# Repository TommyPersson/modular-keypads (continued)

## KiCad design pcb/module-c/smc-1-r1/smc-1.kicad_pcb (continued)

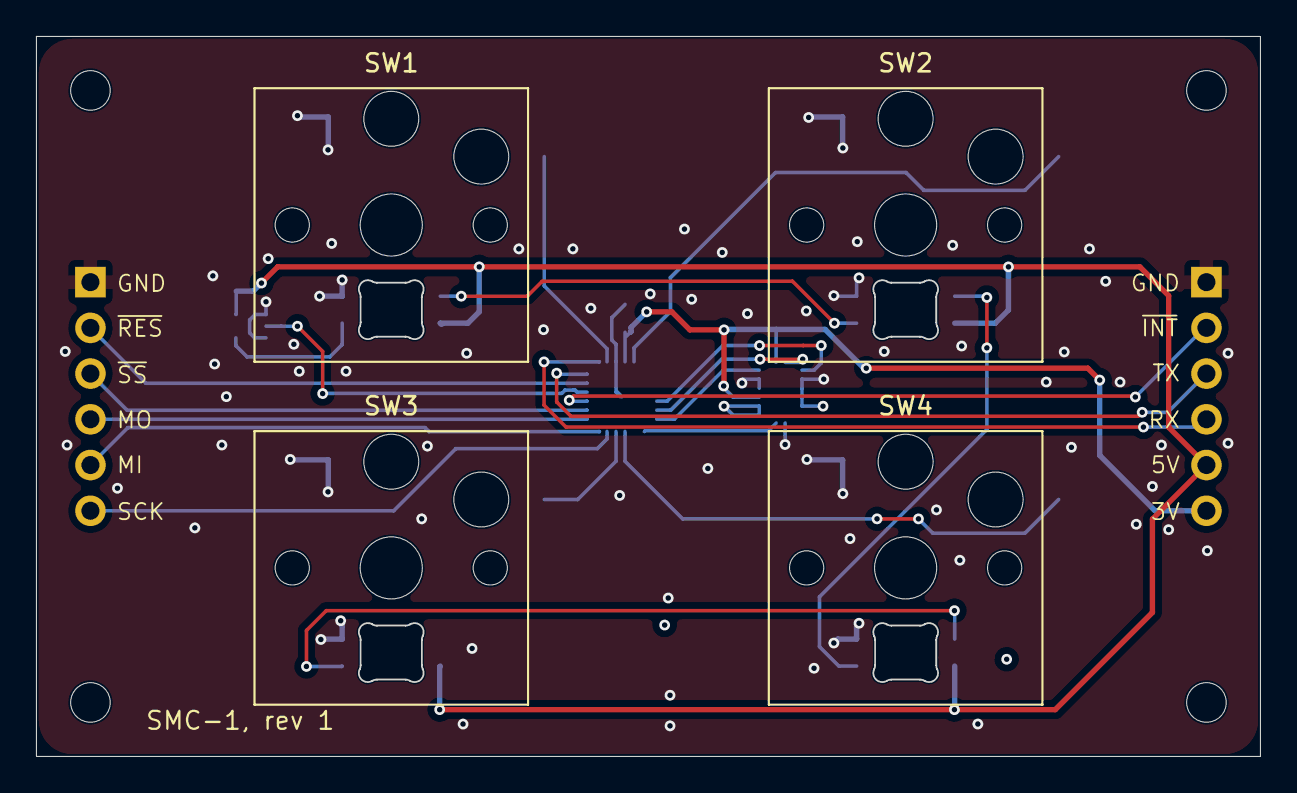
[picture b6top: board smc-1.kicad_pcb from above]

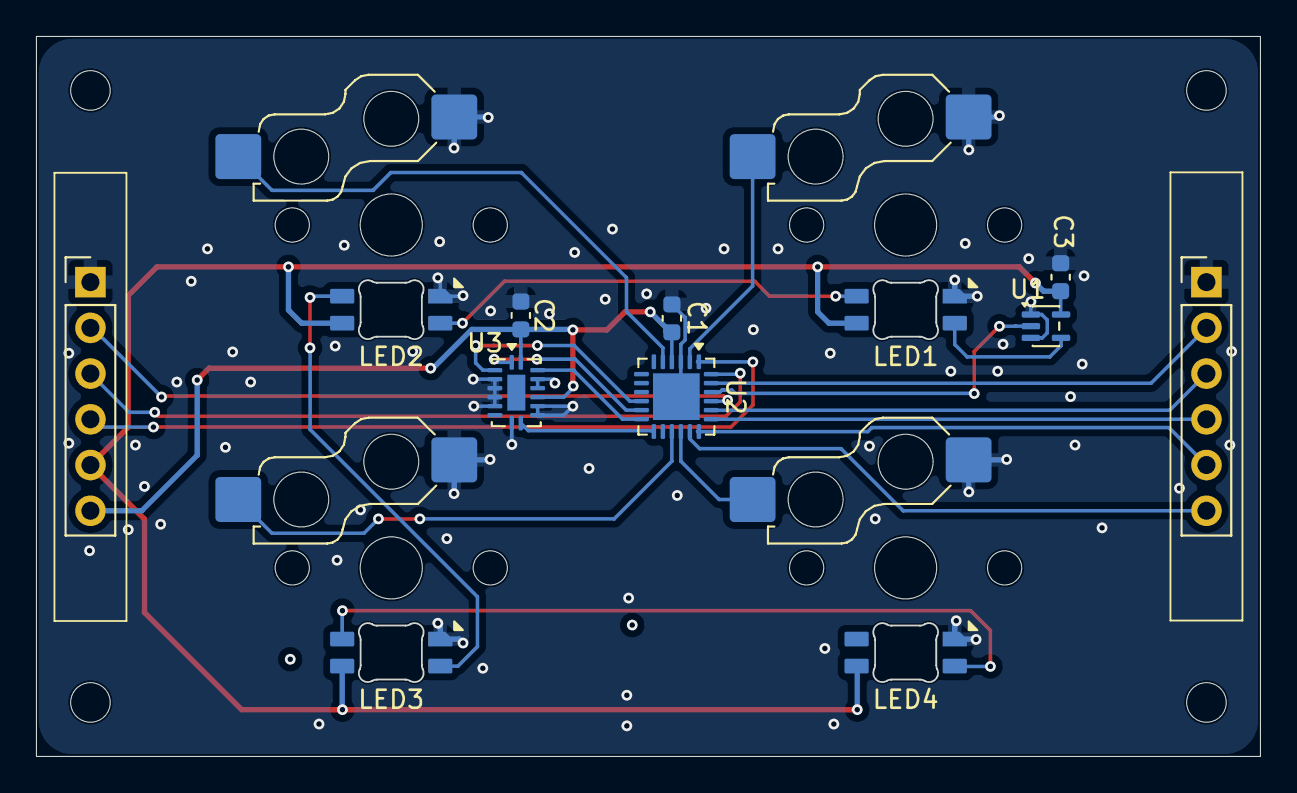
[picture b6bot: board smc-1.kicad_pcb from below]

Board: 4 copper layers, 68.0 x 40.0 mm, 20 parts (12 on the bottom side), 24 nets.

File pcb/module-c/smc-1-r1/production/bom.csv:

Designator,Footprint,Quantity,Value,LCSC Part #
"C1, C2",0603,2,0.1,
C3,0603,1,0.1 uF,
"J1, J3",PinHeader_1x06_P2.54mm_Vertical,2,Conn_01x06,
"LED1, LED2, LED3, LED4, LED5, LED6",LED_choc_6028R-ROT,6,SK6812MINI-E,
"SW1, SW2, SW3, SW4, SW5, SW6",SW_Hotswap_Kailh_Choc_V1_1.00u,6,SW_Push,
U1,SOT-353_SC-70-5,1,74AHCT1G125,
U2,QFN-24-1EP_4x4mm_P0.5mm_EP2.6x2.6mm,1,ATtiny1616-M,
U3,DHVQFN-16-1EP_2.5x3.5mm_P0.5mm_EP1x2mm,1,74HC165,
